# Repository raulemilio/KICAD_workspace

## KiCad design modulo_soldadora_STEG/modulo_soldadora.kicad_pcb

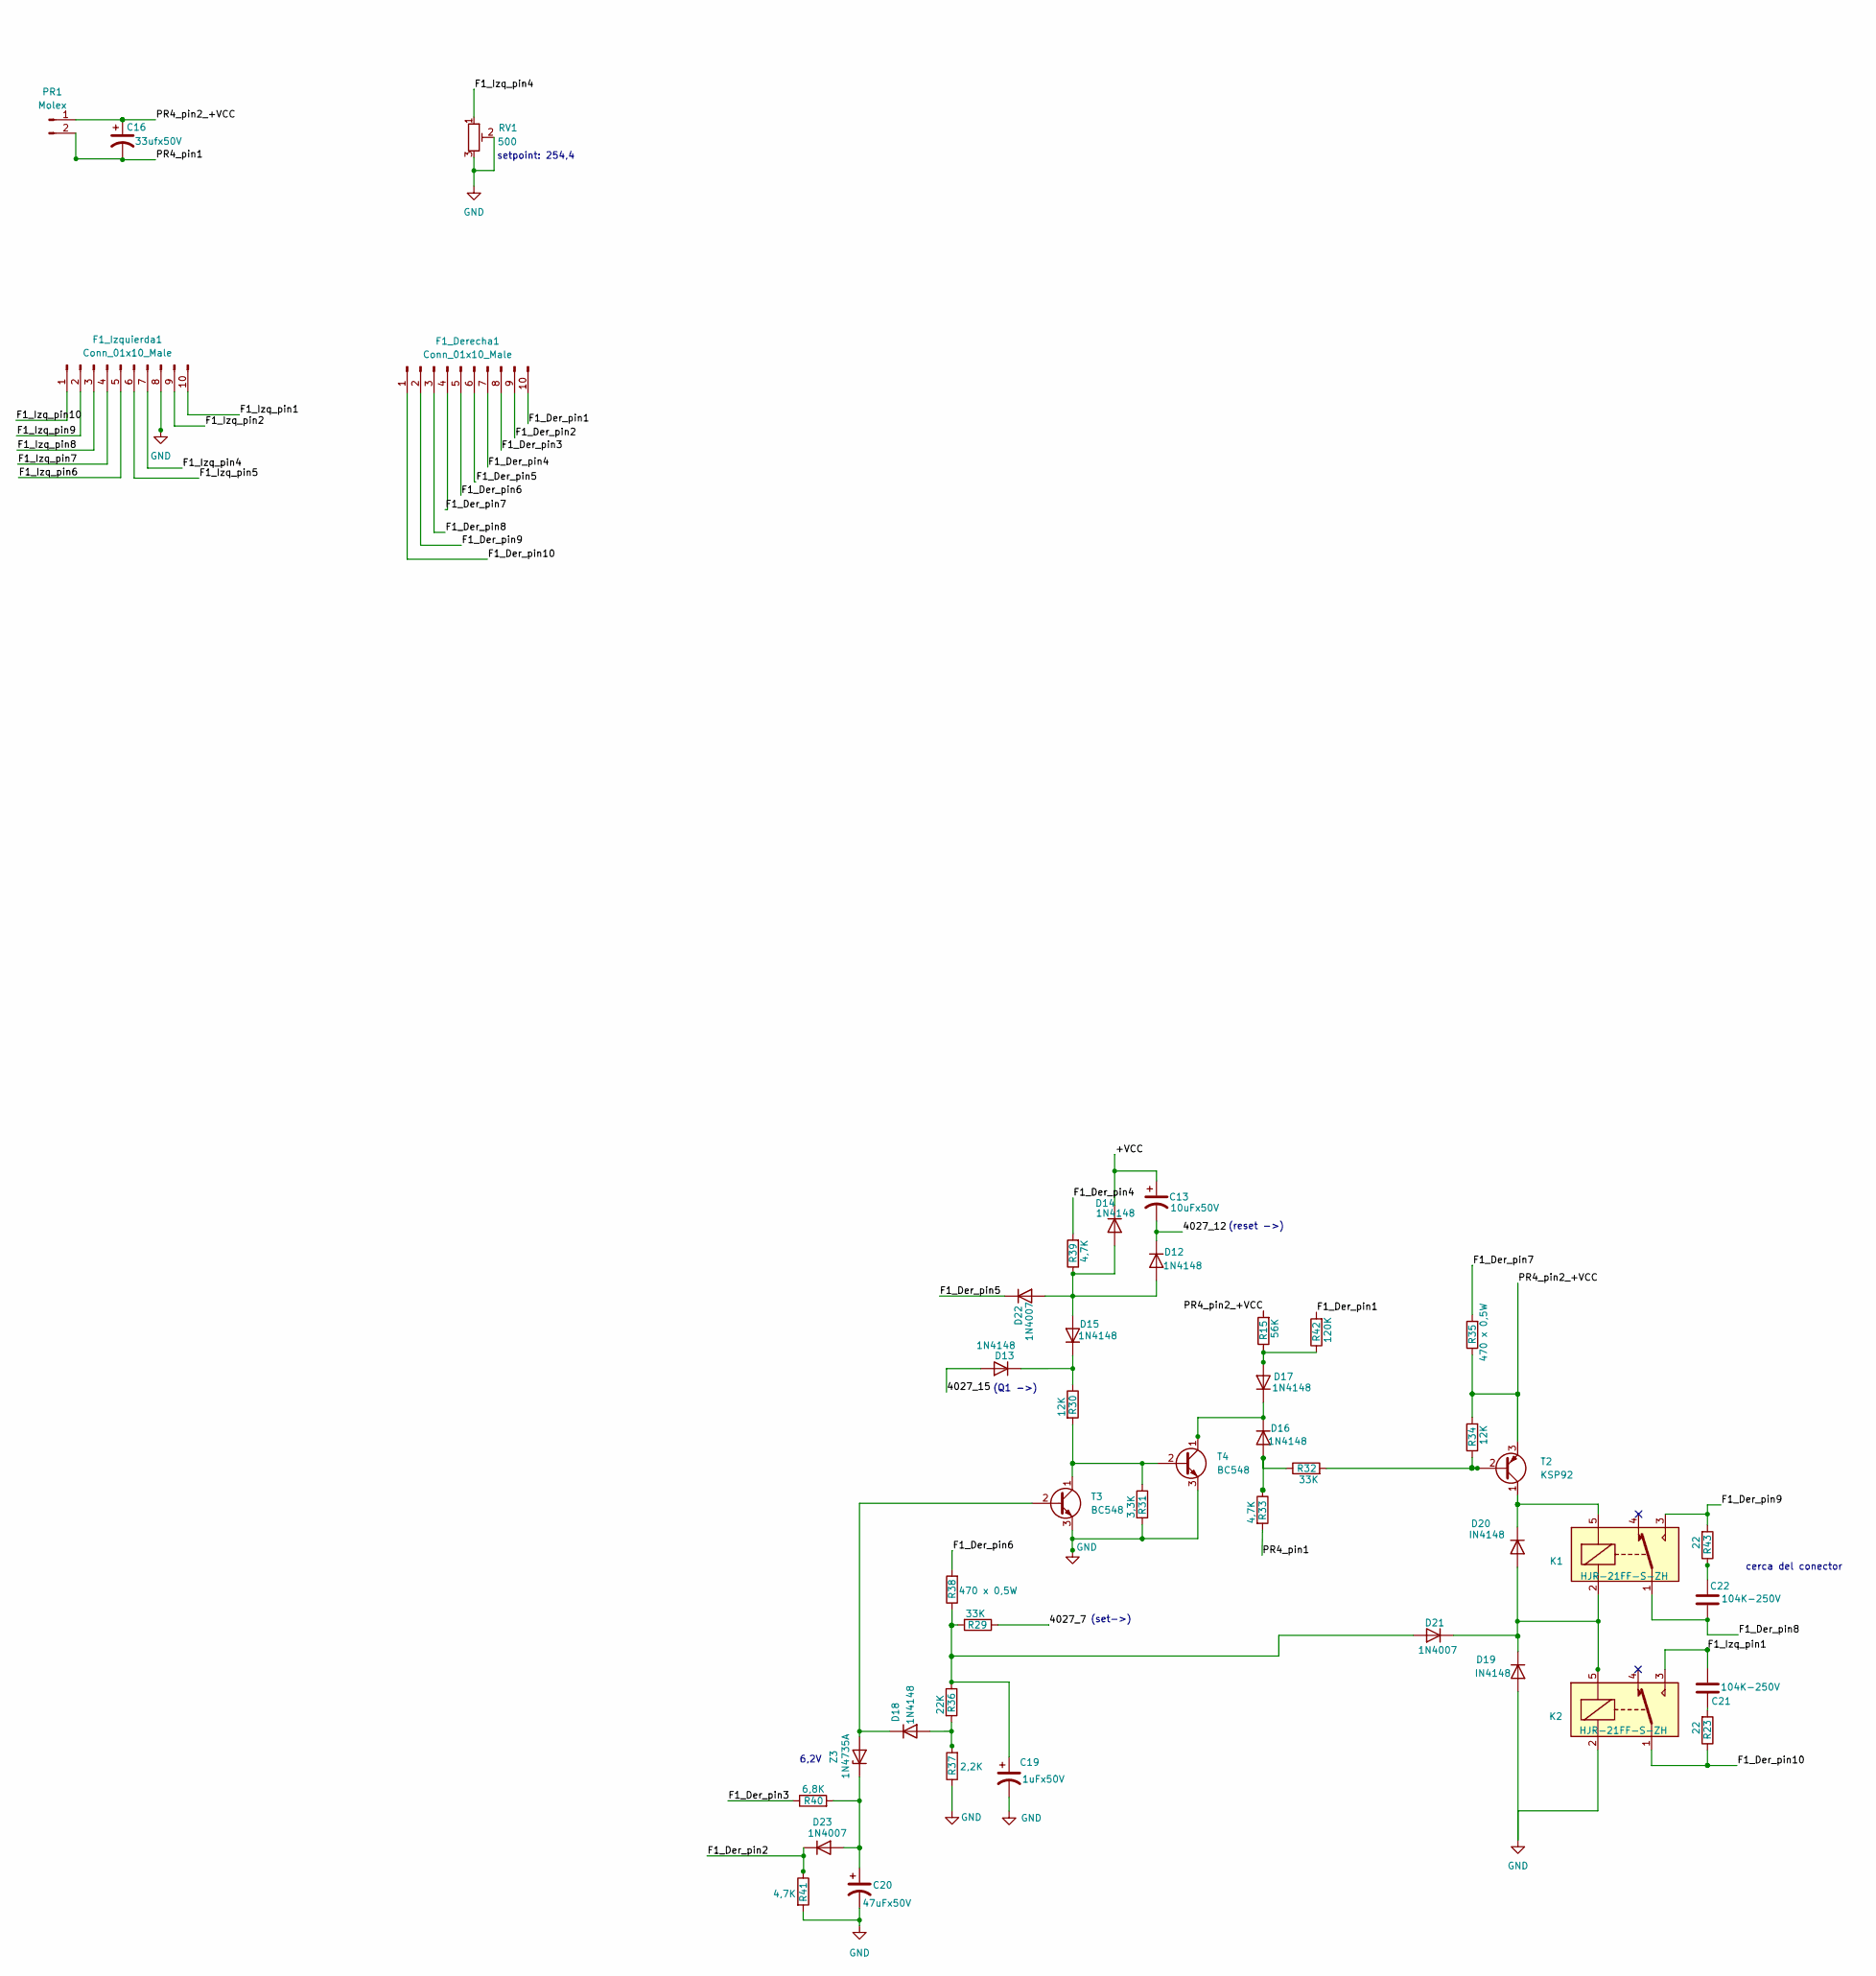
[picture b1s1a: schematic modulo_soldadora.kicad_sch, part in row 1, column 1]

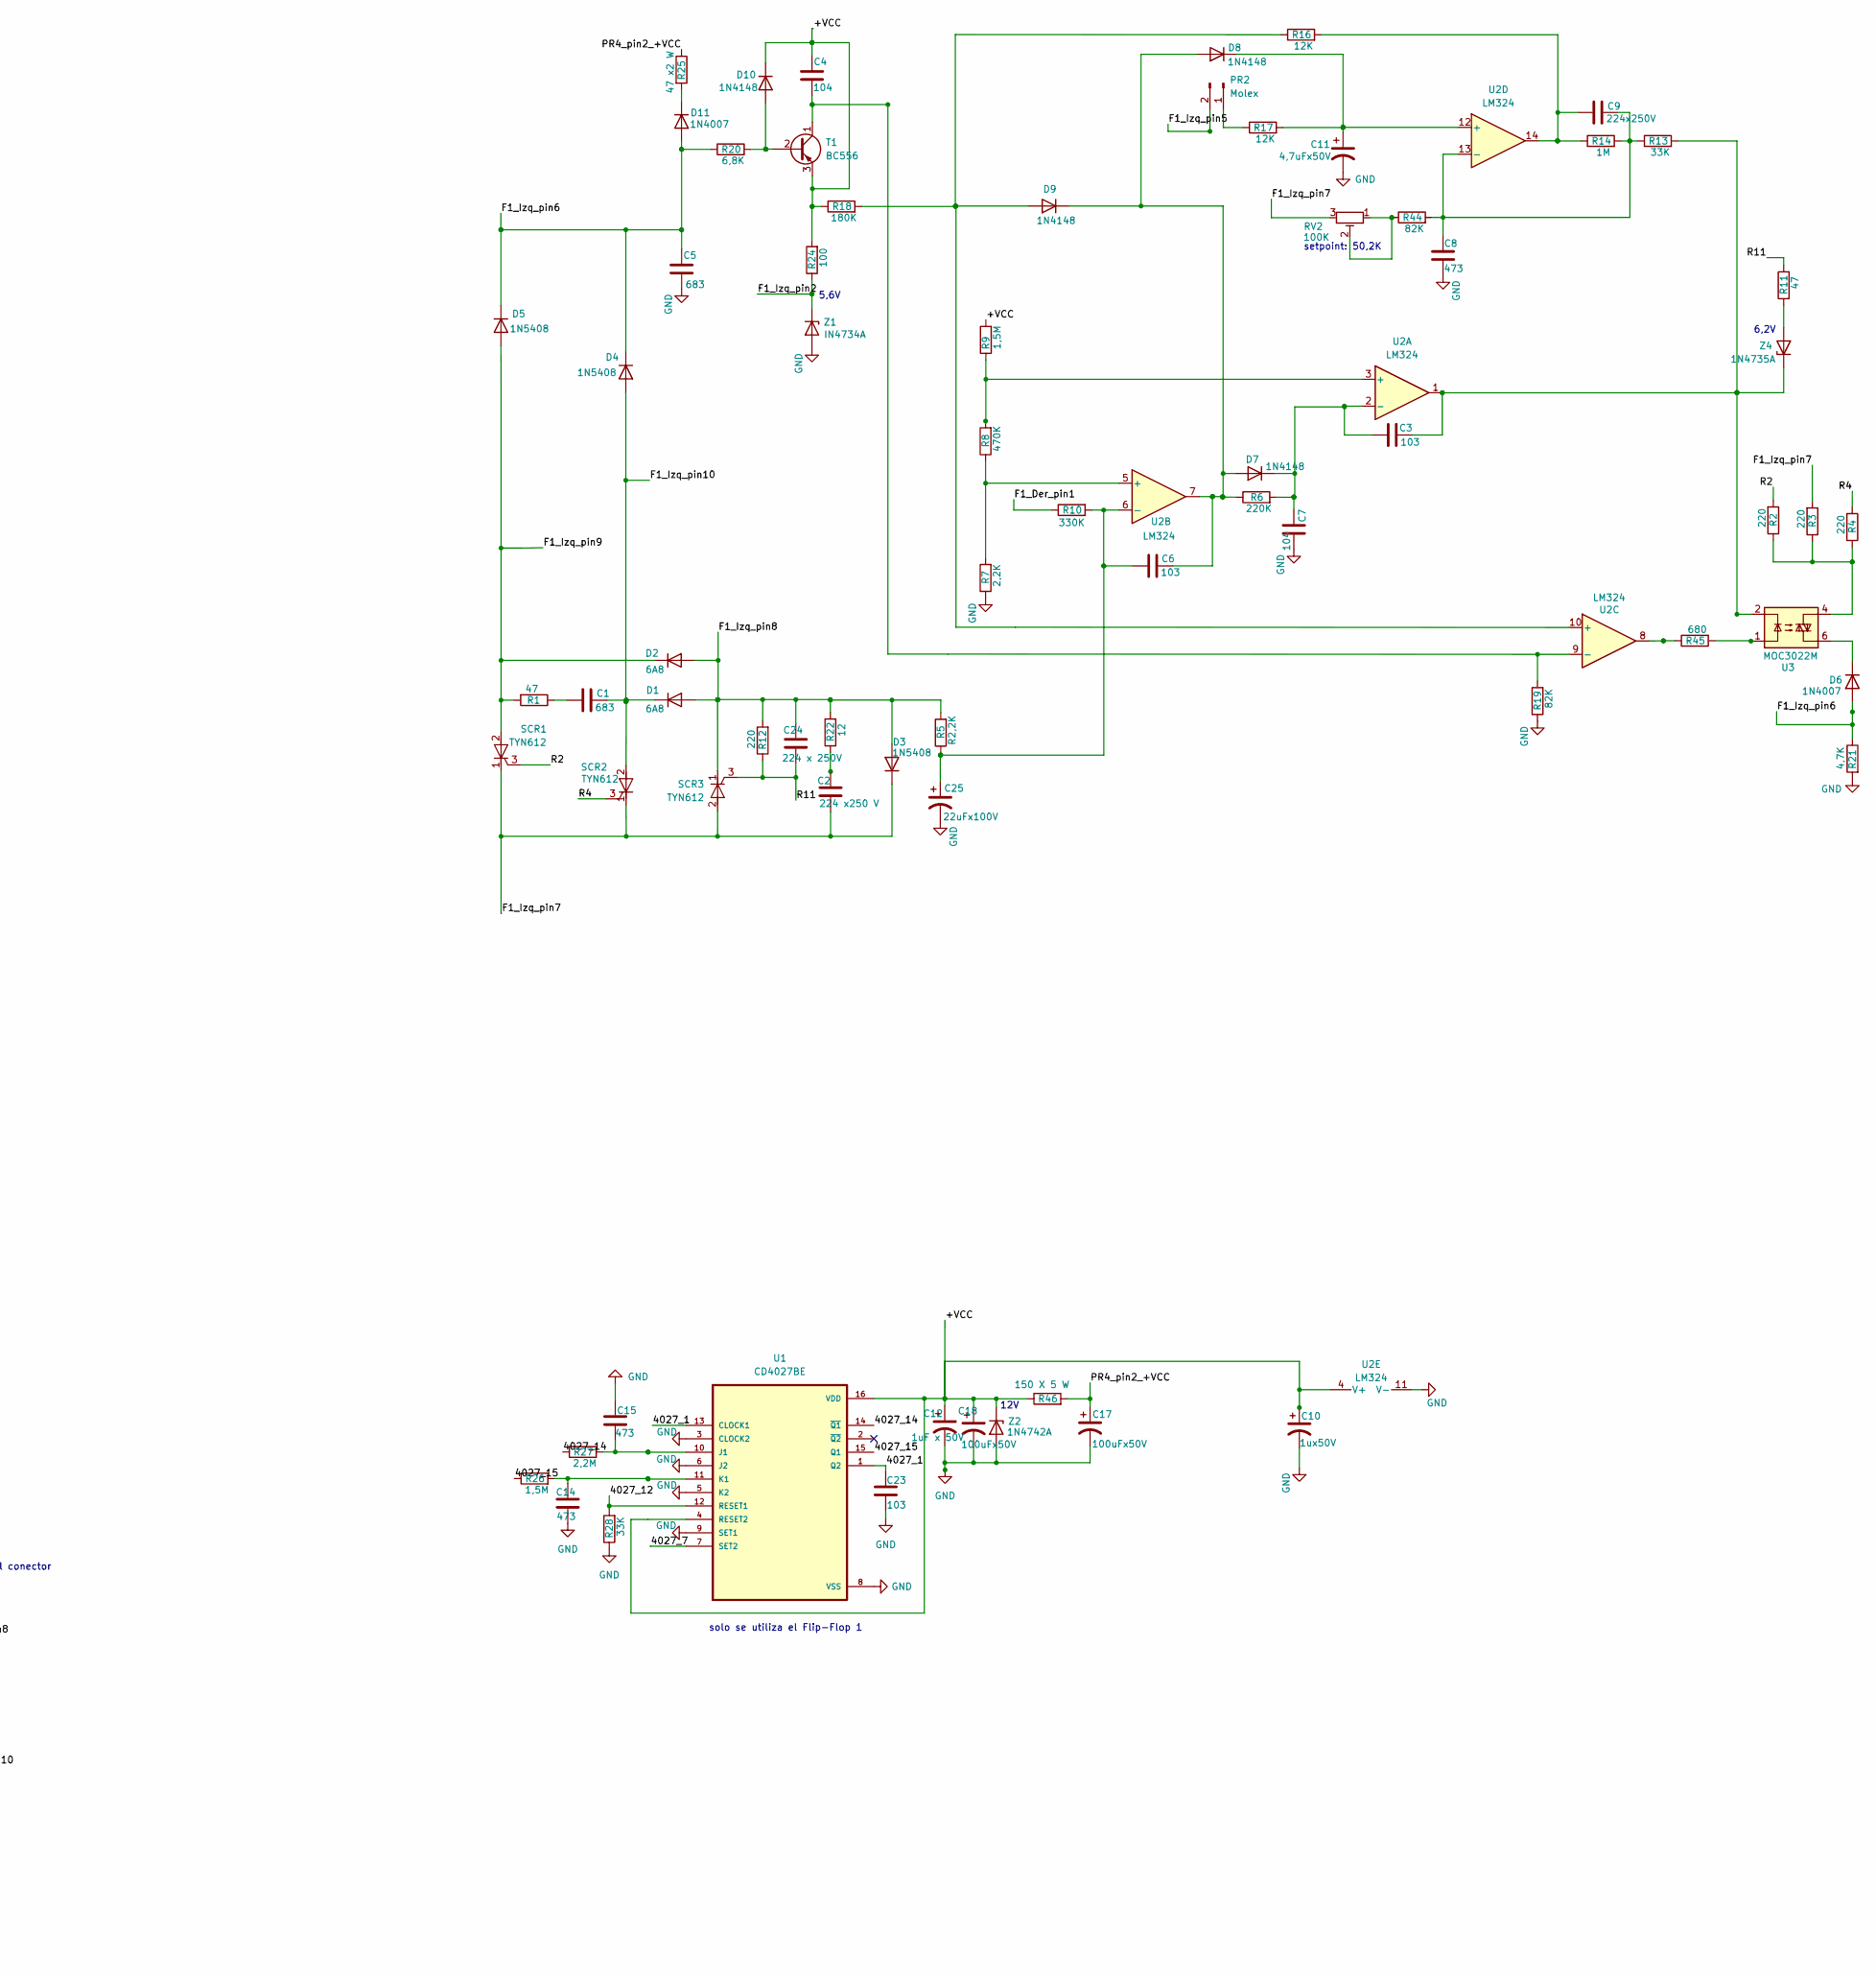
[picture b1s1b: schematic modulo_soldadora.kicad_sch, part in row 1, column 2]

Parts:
C1, C5: 683; C_Disc_D8.0mm_W5.0mm_P7.50mm
C2: 224 x250 V; C_Disc_D8.0mm_W5.0mm_P7.50mm
C3, C6, C23: 103; C_Disc_D8.0mm_W5.0mm_P7.50mm
C4, C7: 104; C_Disc_D8.0mm_W5.0mm_P7.50mm
C8, C15: 473; C_Disc_D8.0mm_W5.0mm_P7.50mm
C9: 224x250V; C_Disc_D8.0mm_W5.0mm_P7.50mm
C10: 1ux50V; CP_Radial_D5.0mm_P2.50mm
C11: 4,7uFx50V; CP_Radial_D5.0mm_P2.50mm
C12: 1uF x 50V; CP_Radial_D5.0mm_P2.50mm
C13: 10uFx50V; CP_Radial_D5.0mm_P2.50mm
C14: 473; C_Disc_D10.5mm_W5.0mm_P7.50mm
C16: 33ufx50V; CP_Radial_D5.0mm_P2.50mm
C17, C18: 100uFx50V; CP_Radial_D10.0mm_P2.50mm
C19: 1uFx50V; CP_Radial_D5.0mm_P2.50mm
C20: 47uFx50V; CP_Radial_D5.0mm_P2.50mm
C21, C22: 104K-250V; C_Disc_D8.0mm_W5.0mm_P7.50mm
C24: 224 x 250V; C_Disc_D8.0mm_W5.0mm_P7.50mm
C25: 22uFx100V; CP_Radial_D5.0mm_P2.50mm
D1, D2: 6A8; D_P600_R-6_P20.00mm_Horizontal
D3, D4, D5: 1N5408; D_P600_R-6_P20.00mm_Horizontal
D6, D11, D21, D22, D23: 1N4007; D_5W_P10.16mm_Horizontal
D7, D8, D9, D10, D12, D13, D14, D15, D16, D17, D18: 1N4148; D_5W_P10.16mm_Horizontal
D19, D20: IN4148; D_5W_P10.16mm_Horizontal
F1_Derecha1, F1_Izquierda1: Conn_01x10_Male; JST_VH_B10P-VH-B_1x10_P3.96mm_Vertical
K1, K2: HJR-21FF-S-ZH; Relay_SPDT_SANYOU_SRD_Series_Form_C
PR1, PR2: Molex; JST_VH_B2P-VH_1x02_P3.96mm_Vertical
R1, R11: 47; R_Axial_DIN0309_L9.0mm_D3.2mm_P12.70mm_Horizontal
R2, R3, R4, R12: 220; R_Axial_DIN0309_L9.0mm_D3.2mm_P12.70mm_Horizontal
R5: R2,2K; R_Axial_DIN0309_L9.0mm_D3.2mm_P12.70mm_Horizontal
R6: 220K; R_Axial_DIN0309_L9.0mm_D3.2mm_P12.70mm_Horizontal
R7, R37: 2,2K; R_Axial_DIN0309_L9.0mm_D3.2mm_P12.70mm_Horizontal
R8: 470K; R_Axial_DIN0309_L9.0mm_D3.2mm_P12.70mm_Horizontal
R9, R26: 1,5M; R_Axial_DIN0309_L9.0mm_D3.2mm_P12.70mm_Horizontal
R10: 330K; R_Axial_DIN0309_L9.0mm_D3.2mm_P12.70mm_Horizontal
R13, R28, R29, R32: 33K; R_Axial_DIN0309_L9.0mm_D3.2mm_P12.70mm_Horizontal
R14: 1M; R_Axial_DIN0309_L9.0mm_D3.2mm_P12.70mm_Horizontal
R15: 56K; R_Axial_DIN0309_L9.0mm_D3.2mm_P12.70mm_Horizontal
R16, R17, R30, R34: 12K; R_Axial_DIN0309_L9.0mm_D3.2mm_P12.70mm_Horizontal
R18: 180K; R_Axial_DIN0309_L9.0mm_D3.2mm_P12.70mm_Horizontal
R19, R44: 82K; R_Axial_DIN0309_L9.0mm_D3.2mm_P12.70mm_Horizontal
R20: 6,8K; R_Axial_DIN0207_L6.3mm_D2.5mm_P15.24mm_Horizontal
R21, R33, R39, R41: 4,7K; R_Axial_DIN0309_L9.0mm_D3.2mm_P12.70mm_Horizontal
R22: 12; R_Axial_DIN0309_L9.0mm_D3.2mm_P12.70mm_Horizontal
R23, R43: 22; R_Axial_DIN0309_L9.0mm_D3.2mm_P12.70mm_Horizontal
R24: 100; R_Axial_DIN0309_L9.0mm_D3.2mm_P12.70mm_Horizontal
R25: 47 x2 W; R_Axial_DIN0516_L15.5mm_D5.0mm_P20.32mm_Horizontal
R27: 2,2M; R_Axial_DIN0309_L9.0mm_D3.2mm_P12.70mm_Horizontal
R31: 3,3K; R_Axial_DIN0309_L9.0mm_D3.2mm_P12.70mm_Horizontal
R35, R38: 470 x 0,5W; R_Axial_DIN0309_L9.0mm_D3.2mm_P12.70mm_Horizontal
R36: 22K; R_Axial_DIN0309_L9.0mm_D3.2mm_P12.70mm_Horizontal
R40: 6,8K; R_Axial_DIN0309_L9.0mm_D3.2mm_P12.70mm_Horizontal
R42: 120K; R_Axial_DIN0309_L9.0mm_D3.2mm_P12.70mm_Horizontal
R45: 680; R_Axial_DIN0309_L9.0mm_D3.2mm_P12.70mm_Horizontal
R46: 150 X 5 W; R_Axial_DIN0516_L15.5mm_D5.0mm_P25.40mm_Horizontal
RV1: 500; Potentiometer_Piher_PT-10-V10_Vertical
RV2: 100K; Potentiometer_Piher_PT-10-V10_Vertical
SCR1, SCR2, SCR3: TYN612; TO-220-3_Vertical
T1: BC556; TO-92_Inline
T2: KSP92; TO-92_Inline
T3, T4: BC548; TO-92_Inline
U1: CD4027BE; DIP-16_W7.62mm_LongPads
U2: LM324; DIP-14_W7.62mm_Socket_LongPads
U3: MOC3022M; DIP-6_W7.62mm
Z1: IN4734A; D_5W_P10.16mm_Horizontal
Z2: 1N4742A; D_5W_P10.16mm_Horizontal
Z3, Z4: 1N4735A; D_5W_P10.16mm_Horizontal

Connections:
/4027_1: C23.2, U1.1 (Q2), U1.13 (CLOCK1)
/4027_7: R29.1, U1.7 (SET2)
/4027_12: C13.2, D12.1 (K), R28.2, U1.12 (RESET1)
/4027_14: R27.1, U1.14 (~Q1)
/4027_15: D13.2 (A), R26.1, U1.15 (Q1)
/+VCC: C4.1, C10.1, C12.1, C13.1, C18.1, D10.1 (K), D14.1 (K), R9.2, R18.1, R24.2, R46.1, T1.3 (E), U1.4 (RESET2), U1.16 (VDD), U2.4 (V+), Z2.1 (K)
/F1_Der_pin1: F1_Derecha1.10, R10.1, R42.2
/F1_Der_pin2: D23.1 (K), F1_Derecha1.9, R41.1
/F1_Der_pin3: F1_Derecha1.8, R40.1
/F1_Der_pin4: F1_Derecha1.7, R39.2
/F1_Der_pin5: D22.1 (K), F1_Derecha1.6
/F1_Der_pin6: F1_Derecha1.5, R38.2
/F1_Der_pin7: F1_Derecha1.4, R35.2
/F1_Der_pin8: C22.2, F1_Derecha1.3, K1.1
/F1_Der_pin9: F1_Derecha1.2, K1.3, R43.2
/F1_Der_pin10: F1_Derecha1.1, K2.1, R23.1
/F1_Izq_pin1: C21.1, F1_Izquierda1.10, K2.3
/F1_Izq_pin2: F1_Izquierda1.9, R24.1, Z1.1 (K)
/F1_Izq_pin4: F1_Izquierda1.7, RV1.1
/F1_Izq_pin5: F1_Izquierda1.6, PR2.2
/F1_Izq_pin6: C5.1, D4.1 (K), D5.1 (K), D6.2 (A), D11.2 (A), F1_Izquierda1.5, R20.1, R21.1
/F1_Izq_pin7: C2.2, D3.1 (K), F1_Izquierda1.4, R3.2, RV2.3, SCR1.1 (K), SCR2.1 (K), SCR3.2 (A)
/F1_Izq_pin8: C24.1, D1.2 (A), D2.2 (A), D3.2 (A), F1_Izquierda1.3, R5.2, R12.2, R22.2, SCR3.1 (K)
/F1_Izq_pin9: D2.1 (K), D5.2 (A), F1_Izquierda1.2, R1.2, SCR1.2 (A)
/F1_Izq_pin10: C1.2, D1.1 (K), D4.2 (A), F1_Izquierda1.1, SCR2.2 (A)
/PR4_pin1: C16.2, PR1.2, R33.2
/PR4_pin2_+VCC: C16.1, C17.1, PR1.1, R15.2, R25.1, R34.2, R35.1, R46.2, T2.3 (E)
/R2: R2.2, SCR1.3 (G)
/R4: R4.2, SCR2.3 (G)
/R11: C24.2, R11.2, R12.1, SCR3.3 (G)
GND: C5.2, C7.2, C8.1, C10.2, C11.2, C12.2, C14.1, C15.2, C17.2, C18.2, C19.2, C20.2, C23.1, C25.2, D19.2 (A), F1_Izquierda1.8, K2.2, R7.1, R19.1, R21.2, R28.1, R31.2, R37.1, R41.2, RV1.2, RV1.3, T3.3 (E), T4.3 (E), U1.3 (CLOCK2), U1.5 (K2), U1.6 (J2), U1.8 (VSS), U1.9 (SET1), U2.11 (V-), Z1.2 (A), Z2.2 (A)
unnamed: C1.1, R1.1
unnamed: C2.1, R22.1
unnamed: C3.1, R13.2, U2.1, U3.2, Z4.1 (K)
unnamed: C3.2, C7.1, D7.1 (K), R6.2, U2.2 (-)
unnamed: C4.2, R19.2, T1.1 (C), U2.9 (-)
unnamed: C6.1, D7.2 (A), D8.2 (A), D9.1 (K), R6.1, U2.7
unnamed: C8.2, C9.1, R13.1, R14.2, R44.2, U2.13 (-)
unnamed: C9.2, R14.1, R16.2, U2.14
unnamed: C11.1, D8.1 (K), R17.2, U2.12 (+)
unnamed: C14.2, R26.2, U1.11 (K1)
unnamed: C15.1, R27.2, U1.10 (J1)
unnamed: C19.1, D21.2 (A), R29.2, R36.1, R38.1
unnamed: C20.1, D23.2 (A), R40.2, Z3.1 (K)
unnamed: C21.2, R23.2
unnamed: C6.2, C25.1, R5.1, R10.2, U2.6 (-)
unnamed: D6.1 (K), U3.6
unnamed: D9.2 (A), R16.1, R18.2, U2.10 (+)
unnamed: D10.2 (A), R20.2, T1.2 (B)
unnamed: D11.1 (K), R25.2
unnamed: D12.2 (A), D14.2 (A), D15.2 (A), D22.2 (A), R39.1
unnamed: D13.1 (K), D15.1 (K), R30.1
unnamed: D16.1 (K), D17.1 (K), T4.1 (C)
unnamed: D16.2 (A), R32.1, R33.1
unnamed: D17.2 (A), R15.1, R42.1
unnamed: D18.1 (K), T3.2 (B), Z3.2 (A)
unnamed: D18.2 (A), R36.2, R37.2
unnamed: D20.1 (K), K1.5, T2.1 (C)
unnamed: D19.1 (K), D20.2 (A), D21.1 (K), K1.2, K2.5
unnamed: PR2.1, R17.1
unnamed: R2.1, R3.1, R4.1, U3.4
unnamed: R7.2, R8.1, U2.5 (+)
unnamed: R8.2, R9.1, U2.3 (+)
unnamed: R11.1, Z4.2 (A)
unnamed: R30.2, R31.1, T3.1 (C), T4.2 (B)
unnamed: R32.2, R34.1, T2.2 (B)
unnamed: C22.1, R43.1
unnamed: R44.1, RV2.1, RV2.2
unnamed: R45.1, U2.8
unnamed: R45.2, U3.1

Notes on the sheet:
cerca del conector
5,6V
6,2V
(Q1 ->)
(reset ->)
(set->)
setpoint: 254,4
solo se utiliza el Flip-Flop 1
12V
setpoint: 50,2K

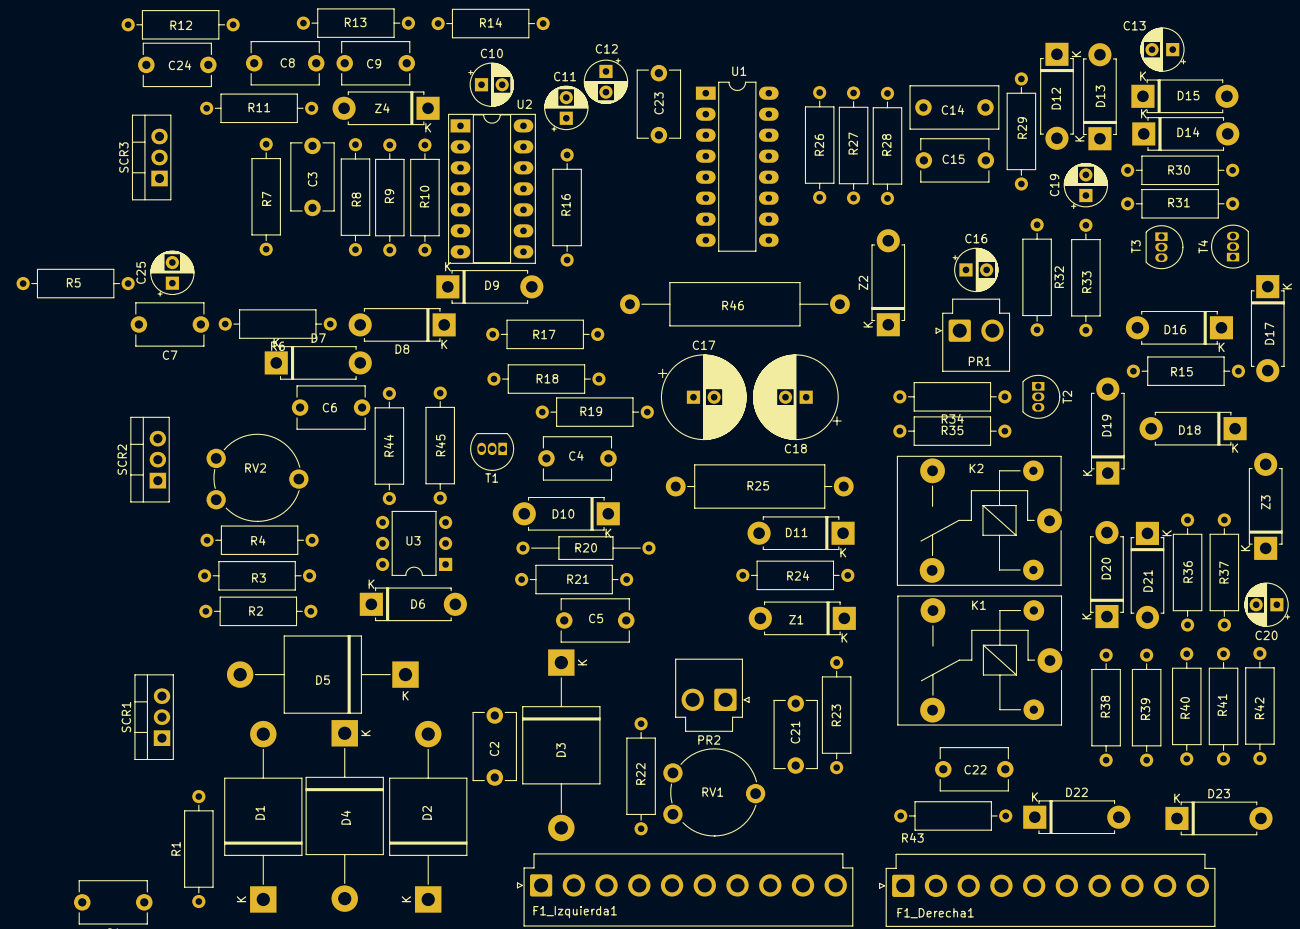
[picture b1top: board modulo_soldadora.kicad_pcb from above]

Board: 2 copper layers, 116 parts (0 on the bottom side), 70 nets.

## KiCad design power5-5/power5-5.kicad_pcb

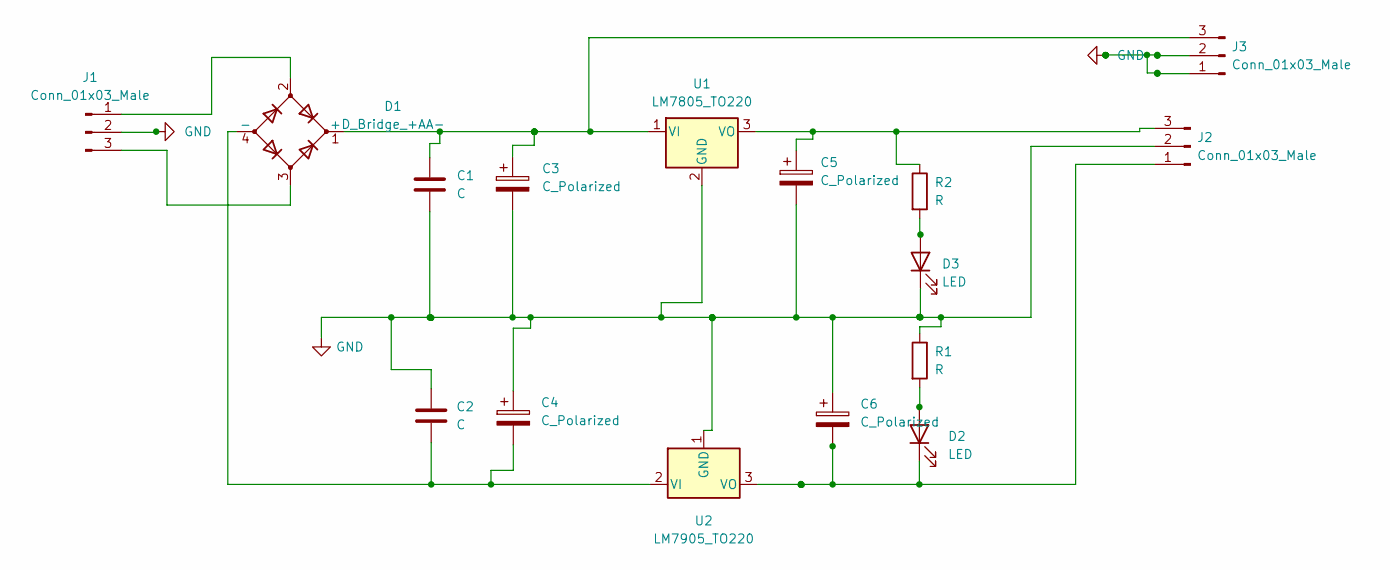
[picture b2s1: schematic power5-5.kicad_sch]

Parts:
C1, C2: C; CP_Radial_D10.0mm_P3.50mm
C3, C4, C5, C6: C_Polarized; CP_Radial_D10.0mm_P5.00mm
D1: D_Bridge_+AA-; Diode_Bridge_19.0x3.5x10.0mm_P5.0mm
D2, D3: LED; LED_D3.0mm_FlatTop
J1, J2, J3: Conn_01x03_Male; PhoenixContact_MCV_1,5_3-G-5.08_1x03_P5.08mm_Vertical
R1, R2: R; R_Axial_DIN0309_L9.0mm_D3.2mm_P12.70mm_Horizontal
U1: LM7805_TO220; TO-220-3_Vertical
U2: LM7905_TO220; TO-220-3_Vertical

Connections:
GND: C1.2, C2.1, C3.2, C4.1, C5.2, C6.1, D3.1 (K), J1.2, J2.2, J3.2, R1.1, U1.2 (GND), U2.1 (GND)
unnamed: C2.2, C4.2, D1.4 (-), U2.2 (VI)
unnamed: C1.1, C3.1, D1.1 (+), J3.3, U1.1 (VI)
unnamed: C5.1, J2.3, R2.1, U1.3 (VO)
unnamed: C6.2, D2.1 (K), J2.1, U2.3 (VO)
unnamed: D2.2 (A), R1.2
unnamed: D3.2 (A), R2.2
unnamed: D1.2, J1.1
unnamed: D1.3, J1.3

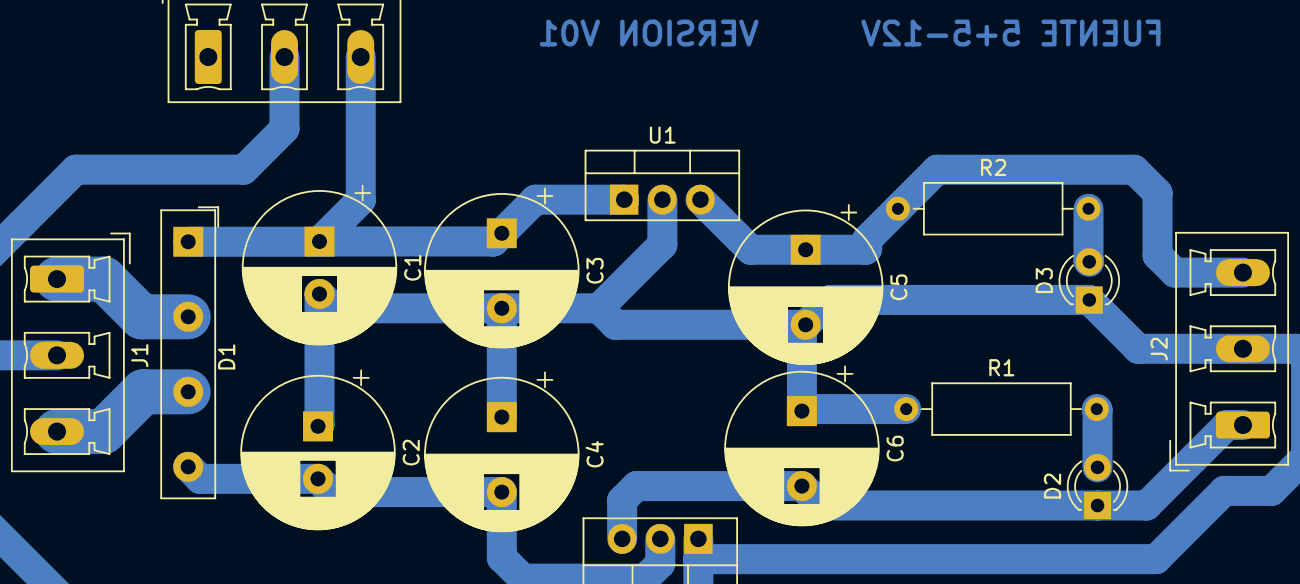
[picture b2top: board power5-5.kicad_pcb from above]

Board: 2 copper layers, 16 parts (0 on the bottom side), 9 nets.

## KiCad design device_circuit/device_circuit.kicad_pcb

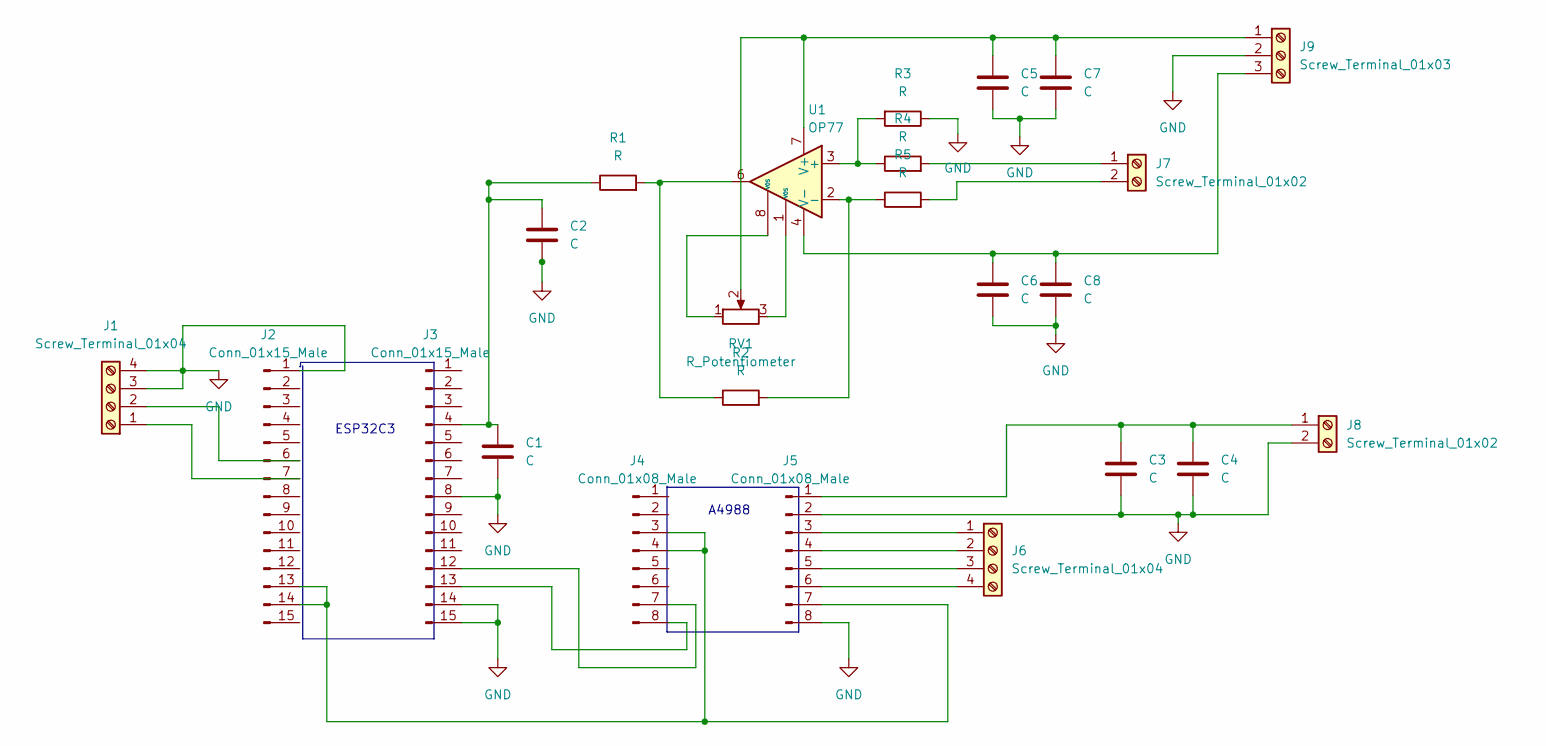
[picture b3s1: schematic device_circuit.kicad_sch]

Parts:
C1, C2, C5, C6, C7, C8: C; CP_Radial_D8.0mm_P5.00mm
C3, C4: C
J1, J6: Screw_Terminal_01x04; PhoenixContact_MCV_1,5_4-G-5.08_1x04_P5.08mm_Vertical
J2, J3: Conn_01x15_Male; PinHeader_1x15_P2.54mm_Vertical
J4, J5: Conn_01x08_Male; PinHeader_1x08_P2.54mm_Vertical
J7, J8: Screw_Terminal_01x02; PhoenixContact_MCV_1,5_2-G-5.08_1x02_P5.08mm_Vertical
J9: Screw_Terminal_01x03; PhoenixContact_MCV_1,5_3-G-5.08_1x03_P5.08mm_Vertical
R1: R
R2, R3, R4, R5: R; R_Axial_DIN0411_L9.9mm_D3.6mm_P12.70mm_Horizontal
RV1: R_Potentiometer
U1: OP77

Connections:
GND: C1.2, C2.2, C3.2, C4.2, C5.2, C6.2, C7.2, C8.2, J1.3, J1.4, J2.1, J3.8, J3.14, J3.15, J5.2, J5.8, J8.2, J9.2, R3.1
unnamed: J1.1, J2.7
unnamed: J1.2, J2.6
unnamed: J2.13, J2.14, J4.3, J4.4, J5.7
unnamed: J3.12, J4.7
unnamed: J3.13, J4.8
unnamed: C3.1, C4.1, J5.1, J8.1
unnamed: J5.3, J6.1
unnamed: J5.4, J6.2
unnamed: J5.5, J6.3
unnamed: J5.6, J6.4
unnamed: J7.1, R4.2
unnamed: J7.2, R5.2
unnamed: C5.1, C7.1, J9.1, RV1.2, U1.7 (V+)
unnamed: C1.1, C2.1, J3.4, R1.1
unnamed: R2.2, R5.1, U1.2 (-)
unnamed: R3.2, R4.1, U1.3 (+)
unnamed: RV1.1, U1.8 (VOS)
unnamed: RV1.3, U1.1 (VOS)
unnamed: C6.1, C8.1, J9.3, U1.4 (V-)
unnamed: R1.2, R2.1, U1.6

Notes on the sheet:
ESP32C3
A4988

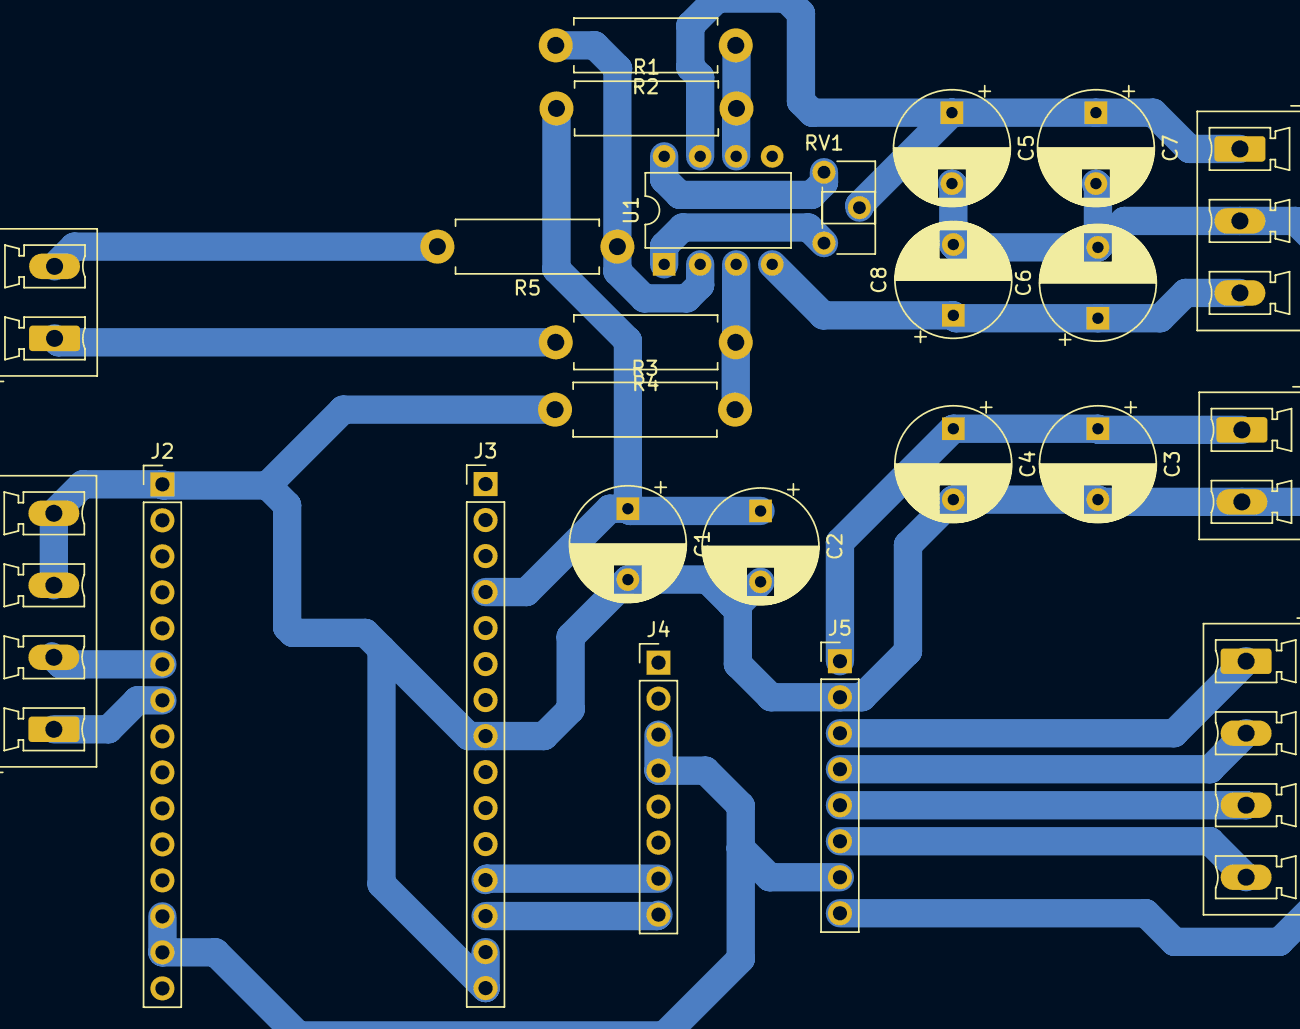
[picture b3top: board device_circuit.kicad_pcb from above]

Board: 2 copper layers, 24 parts (0 on the bottom side), 21 nets.

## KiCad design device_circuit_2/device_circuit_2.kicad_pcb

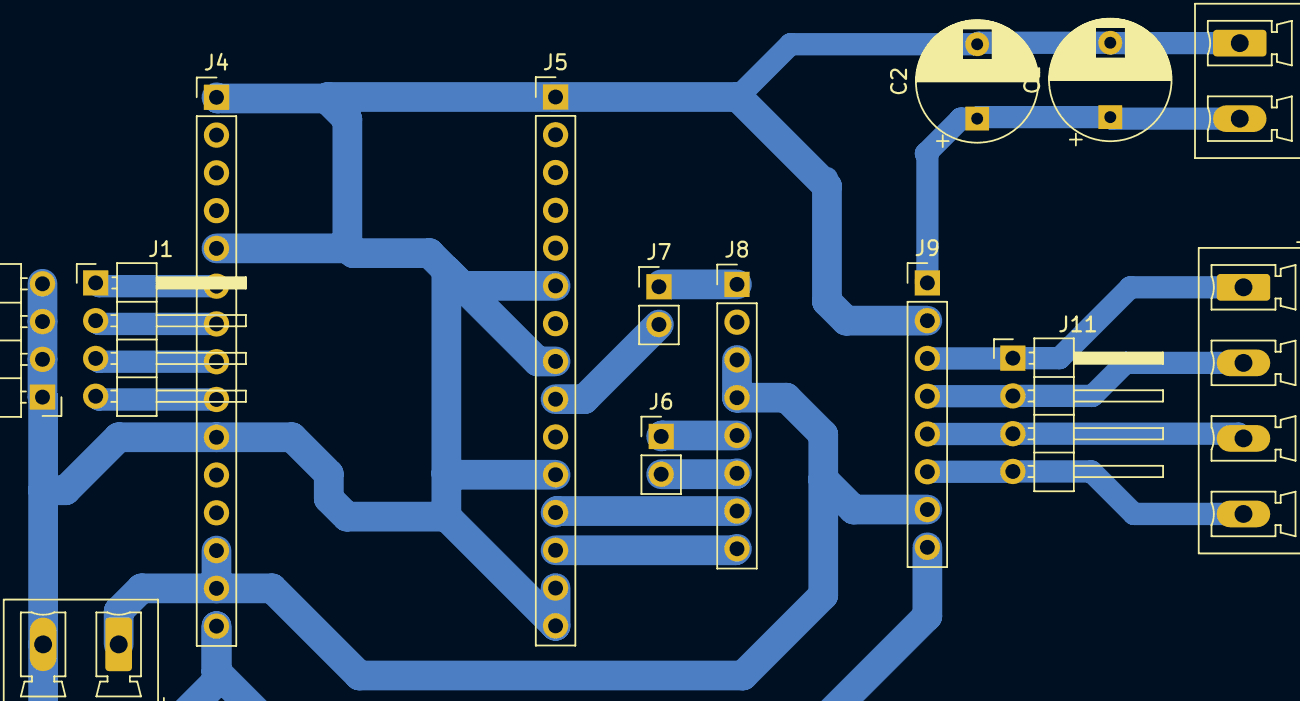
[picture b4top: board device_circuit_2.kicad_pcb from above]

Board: 2 copper layers, 14 parts (0 on the bottom side), 17 nets.

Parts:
C3, C4: C; CP_Radial_D8.0mm_P5.00mm
J1, J2#2, J11: Conn_01x04_Male; PinHeader_1x04_P2.54mm_Horizontal
J2, J3: Conn_01x15_Male; PinHeader_1x15_P2.54mm_Vertical
J4, J5: Conn_01x08_Male; PinHeader_1x08_P2.54mm_Vertical
J6: Screw_Terminal_01x04; PhoenixContact_MCV_1,5_4-G-5.08_1x04_P5.08mm_Vertical
J6#2, J7: Conn_01x02_Male; PinHeader_1x02_P2.54mm_Vertical
J8, J8#2: Screw_Terminal_01x02; PhoenixContact_MCV_1,5_2-G-5.08_1x02_P5.08mm_Vertical

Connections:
GND: C3.2, C4.2, J2.1, J2.5, J2.10, J2.15, J2#2.1, J2#2.2, J2#2.3, J2#2.4, J3.1, J3.6, J3.8, J3.11, J3.14, J3.15, J5.2, J5.8, J8.2, J8#2.1
unnamed: C3.1, C4.1, J5.1, J8#2.2
unnamed: J1.1, J2.6
unnamed: J1.2, J2.7
unnamed: J1.3, J2.8
unnamed: J1.4, J2.9
unnamed: J2.13, J2.14, J4.3, J4.4, J5.7, J8.1
unnamed: J3.9, J7.2
unnamed: J3.12, J4.7
unnamed: J3.13, J4.8
unnamed: J4.5, J6#2.1
unnamed: J4.6, J6#2.2
unnamed: J4.1, J7.1
unnamed: J5.3, J6.1, J11.1
unnamed: J5.4, J6.2, J11.2
unnamed: J5.5, J6.3, J11.3
unnamed: J5.6, J6.4, J11.4

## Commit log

2023-08-21 se agregan los archivos actuales
2023-09-27 actualizado repo
2025-02-10 actua repo
